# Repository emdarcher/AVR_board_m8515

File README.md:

AVR_board_m8515
===============

An AVR development board for the ATmega8515, will probably be used with the [Moppy_AVR](https://github.com/emdarcher/Moppy_AVR) code.

Link to the [Hackaday Projects page](http://hackaday.io/project/3034) for this thing.

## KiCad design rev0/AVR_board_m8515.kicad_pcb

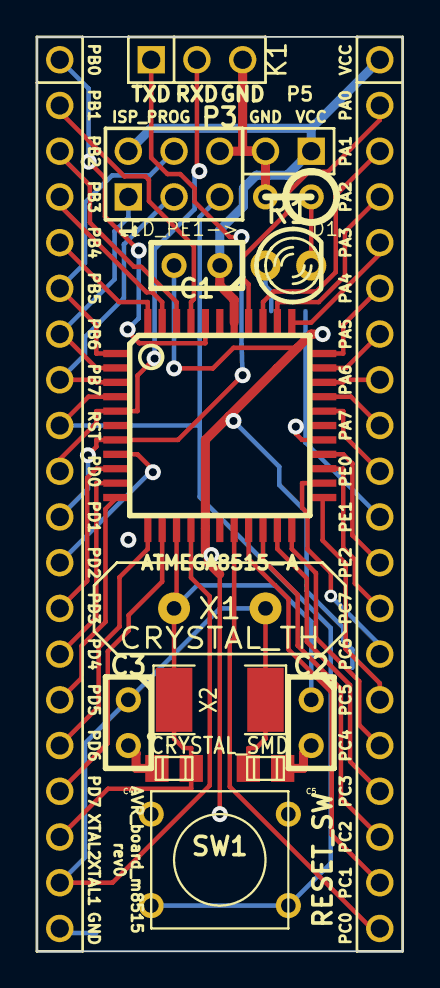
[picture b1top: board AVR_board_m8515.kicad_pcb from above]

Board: 2 copper layers, 20.3 x 50.8 mm, 17 parts (1 on the bottom side), 42 nets.

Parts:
C1: C; C1
C2, C3: CX; C1
C4, C5: CX_SMD; c_0805
D1: LED_PE1->; LED-3MM
IC1: ATMEGA8515-A; TQFP44
JP1: LED_JUMPER; SM0805
K1: SERIAL; PIN_ARRAY_3X1
P2: LEFT_HEADER; pinarray_20x1
P3: CONN_3X2; pin_array_3x2
P4: RIGHT_HEADER; pinarray_20x1
P5: EXT_PWR; PIN_ARRAY_2X1
R1: R; R1
SW1: RESET_SW; SW_PUSH_SMALL
X1: CRYSTAL_TH; HC-18UV
X2: CRYSTAL_SMD; SM1812L

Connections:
GND: C1.2, C2.2, C3.2, C4.2, C5.2, IC1.16, K1.3, P2.20, P3.6, P5.2, R1.2, SW1.1
unnamed: D1.2, R1.1
unnamed: D1.1, JP1.2
PA0: IC1.37, P4.2
PA1: IC1.36, P4.3
PA2: IC1.35, P4.4
PA3: IC1.34, P4.5
PA4: IC1.33, P4.6
PA5: IC1.32, P4.7
PA6: IC1.31, P4.8
PA7: IC1.30, P4.9
PB0: IC1.40, P2.1
PB1: IC1.41, P2.2
PB2: IC1.42, P2.3
PB3: IC1.43, P2.4
PB4: IC1.44, P2.5
PB5: IC1.1, P2.6, P3.4
PB6: IC1.2, P2.7, P3.1
PB7: IC1.3, P2.8, P3.3
PC0: IC1.18, P4.20
PC1: IC1.19, P4.19
PC2: IC1.20, P4.18
PC3: IC1.21, P4.17
PC4: IC1.22, P4.16
PC5: IC1.23, P4.15
PC6: IC1.24, P4.14
PC7: IC1.25, P4.13
PD0: IC1.5, K1.2, P2.10
PD1: IC1.7, K1.1, P2.11
PD2: IC1.8, P2.12
PD3: IC1.9, P2.13
PD4: IC1.10, P2.14
PD5: IC1.11, P2.15
PD6: IC1.12, P2.16
PD7: IC1.13, P2.17
PE0: IC1.29, P4.10
PE1: IC1.27, JP1.1, P4.11
PE2: IC1.26, P4.12
RESET: IC1.4, P2.9, P3.5, SW1.2
VCC: C1.1, IC1.38, P3.2, P4.1, P5.1
XTAL1: C3.1, C5.1, IC1.15, P2.19, X1.2, X2.2
XTAL2: C2.1, C4.1, IC1.14, P2.18, X1.1, X2.1

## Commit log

2014-09-16 starting kicad project for the board
2014-09-16 started schematic, fixed some stuff
2014-09-16 added all needed labels and stuff
2014-09-16 added connections to the labels
2014-09-16 added wires to the things to other mcu pad placeholder thingy
2014-09-17 added isp conn to schematic
2014-09-17 added smd crystal to schematic and an LED on PE1
2014-09-17 made netlist, connected to most footprints
2014-09-17 made a 20x1 pinheader module
2014-09-17 working on PCB design, mostly done with arrangement
2014-09-17 added logo mod file, also added silkscreen refs
2014-09-17 removed the mlf44 footprint due to routing issues
2014-09-17 made ses file after using FreeRouting program to route traces
2014-09-17 trying to fix GND pad disconnects
2014-09-17 fixed GND disconnects, will try to thicken the traces
2014-09-17 change GND track width to 0.02 on most traces
2014-09-17 trying to add more gnd trace connections
2014-09-17 added another GND trace to other GND Plate for niceness
2014-09-17 changed DRC to have some of oshpark's rules
2014-09-17 added some gfx, including oshw logo, also did DRC check
2014-09-17 added an Open-source Hardware License
2014-09-17 generated gerber and drill file, must check though
2014-09-17 put files together for oshpark
2014-09-25 added HaDP link to readme
2014-09-25 added Moppy_AVR repo link to readme
2014-09-29 added a module
